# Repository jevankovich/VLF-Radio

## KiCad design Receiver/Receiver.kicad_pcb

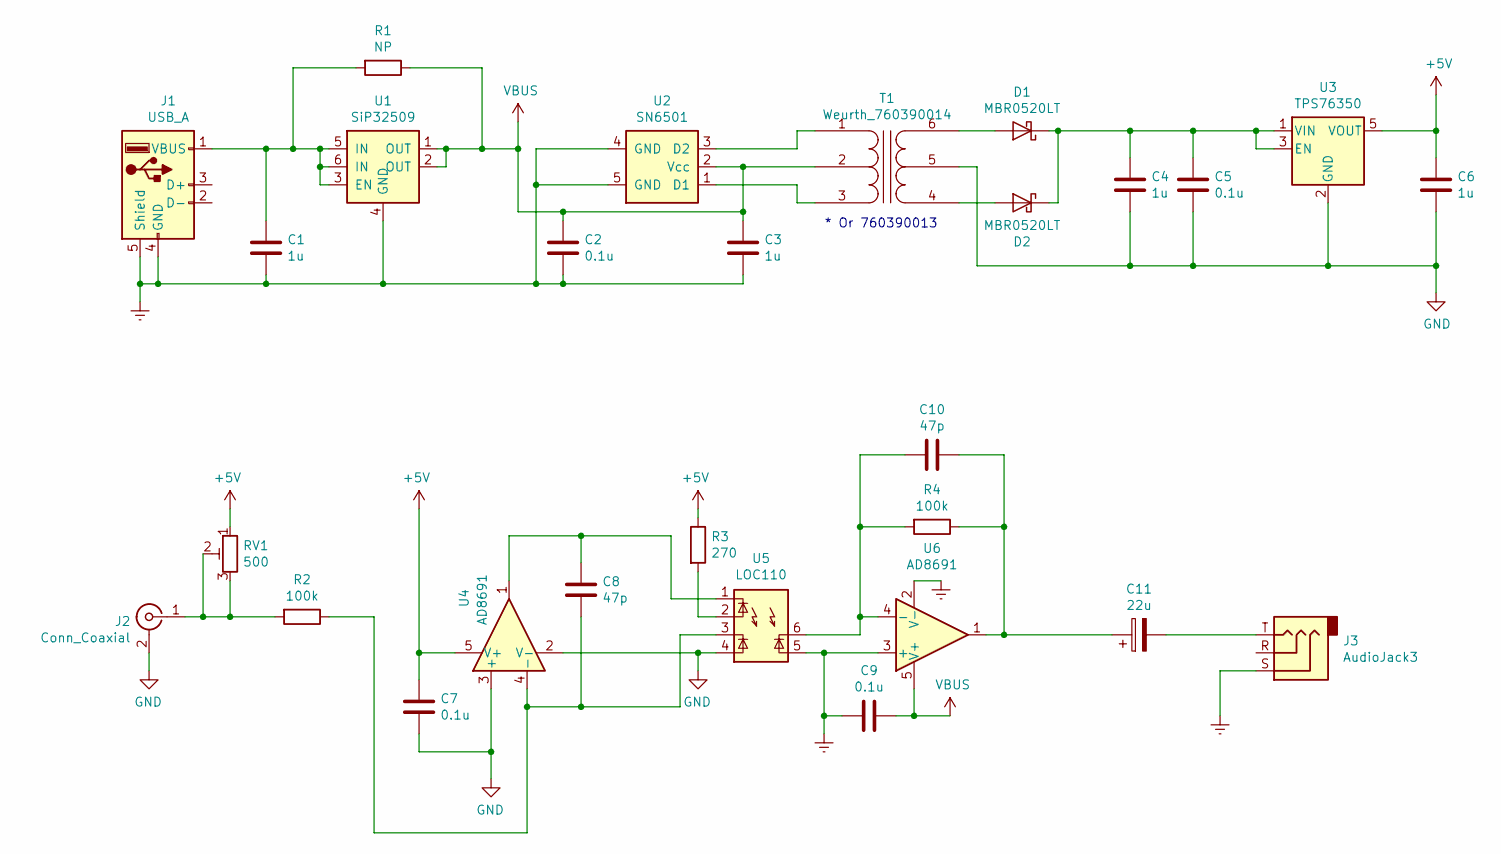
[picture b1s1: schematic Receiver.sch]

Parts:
C1, C3, C4, C6: 1u; C_0805_2012Metric
C2, C5, C7, C9: 0.1u; C_0805_2012Metric
C8, C10: 47p; C_0805_2012Metric
C11: 22u; CP_Radial_D5.0mm_P2.00mm
D1, D2: MBR0520LT; D_SOD-123
J1: USB_A; USB_A_CNCTech_1001-011-01101_Horizontal
J2: Conn_Coaxial; SMA_Amphenol_132289_EdgeMount
J3: AudioJack3; Jack_3.5mm_CUI_SJ-3523-SMT_Horizontal
R1: NP; R_0805_2012Metric
R2, R4: 100k; R_0805_2012Metric
R3: 270; R_0805_2012Metric
RV1: 500; Potentiometer_Bourns_3314G_Vertical
T1: Weurth_760390014
U1: SiP32509; SOT-23-6
U2: SN6501; SOT-23-5
U3: TPS76350; SOT-23-5
U4, U6: AD8691; TSOT-23-5
U5: LOC110; LOC110P

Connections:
+5V: C6.1, C7.2, R3.1, RV1.1, U3.5 (VOUT), U4.5 (V+)
Earth: C1.2, C2.2, C3.2, C9.2, J1.4 (GND), J1.5 (Shield), J3.S, U1.4 (GND), U2.4 (GND), U2.5 (GND), U5.5, U6.2 (V-), U6.3 (+)
GND: C4.2, C5.2, C6.2, C7.1, J2.2 (Ext), T1.5 (OUT1B), U3.2 (GND), U4.2 (V-), U4.3 (+), U5.4
unnamed: C1.1, J1.1 (VBUS), R1.2, U1.3 (EN), U1.5 (IN), U1.6 (IN)
unnamed: C4.1, C5.1, D1.1 (K), D2.1 (K), U3.1 (VIN), U3.3 (EN)
unnamed: C8.1, R2.1, U4.4 (-), U5.3
unnamed: C8.2, U4.1, U5.1
unnamed: C10.1, C11.1, R4.1, U6.1
unnamed: C10.2, R4.2, U5.6, U6.4 (-)
unnamed: C11.2, J3.T
unnamed: D1.2 (A), T1.6 (OUT2A)
unnamed: D2.2 (A), T1.4 (OUT1A)
unnamed: J2.1 (In), R2.2, RV1.2, RV1.3
unnamed: R3.2, U5.2
unnamed: T1.1 (IN+), U2.3 (D2)
unnamed: T1.3 (IN-), U2.1 (D1)
VBUS: C2.1, C3.1, C9.1, R1.1, T1.2 (PM), U1.1 (OUT), U1.2 (OUT), U2.2 (Vcc), U6.5 (V+)

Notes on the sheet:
* Or 760390013

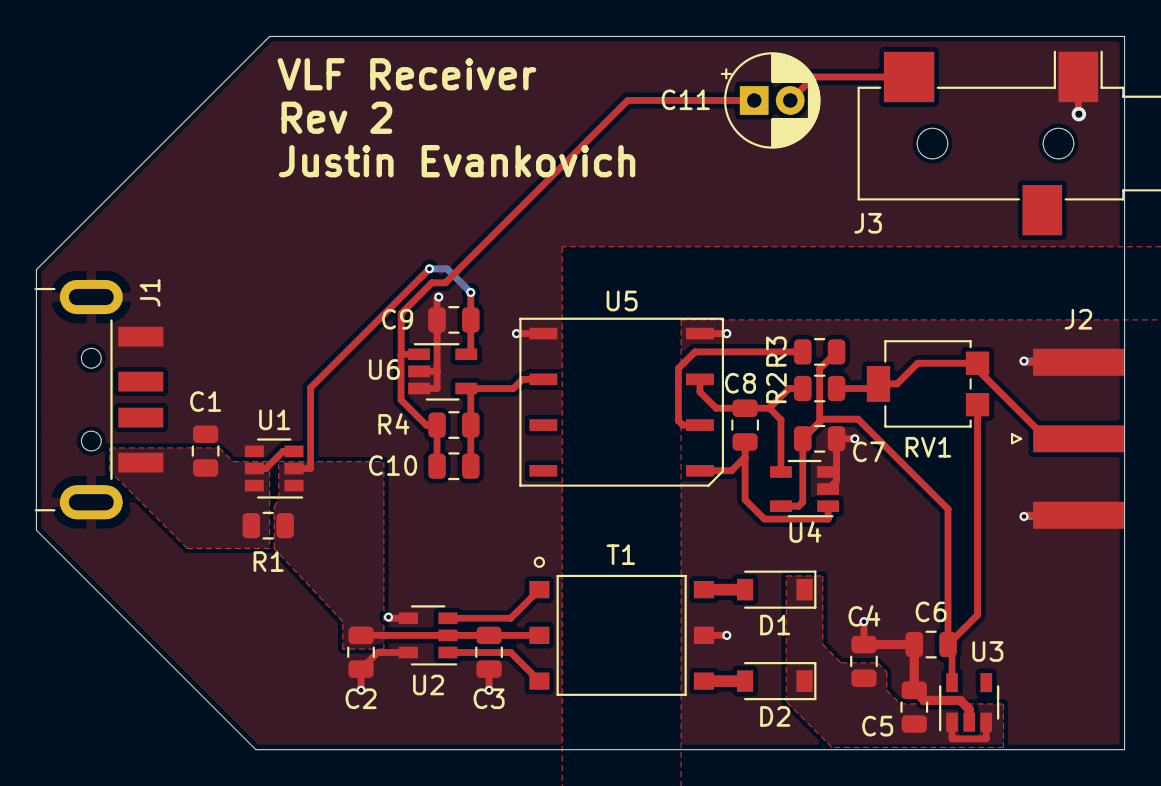
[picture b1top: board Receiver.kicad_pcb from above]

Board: 2 copper layers, 60.5 x 39.6 mm, 28 parts (0 on the bottom side), 17 nets.
